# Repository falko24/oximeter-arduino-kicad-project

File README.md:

<div align="center">

# 🩺 Pulse Oximeter & OLED Interface
### Complete PCB Design for Arduino Nano & MAX30102

*Kompaktowy, dwuwarstwowy moduł PCB pulsooksymetru zintegrowany z wyświetlaczem OLED oraz przyciskami sterującymi.*

</div>

---

## 📸 Podgląd projektu

| Widok 3D (Front) | Widok 3D (Back) |
| :---: | :---: |
|  |  |

---

## 🛠️ Specyfikacja techniczna

* **Mikrokontroler:** Arduino Nano v3 (ATmega328P)
* **Czujnik tętna i SpO2:** MAX30102 (I2C)
* **Wyświetlacz:** OLED 0.96" SSD1306 / 128x64 px (I2C)
* **Interfejs użytkownika:** 3x przyciski Tact Switch ze sprzętową filtracją drgań styków (RC)
* **Wymiary PCB:** 2-warstwowa płyta FR4 (grubość $1.6\text{ mm}$)
* **Zasilanie:** 5V z portu USB Arduino Nano

---

## 🗂️ Struktura repozytorium

```text
.
├── docs/           # Wyrenderowane zdjęcia 3D projektu
├── gerber/         # Paczka produkcyjna (gerber.zip) gotowa do zamówienia
└── hardware/       # Pliki źródłowe KiCad (.kicad_pcb, .kicad_sch, .kicad_pro)

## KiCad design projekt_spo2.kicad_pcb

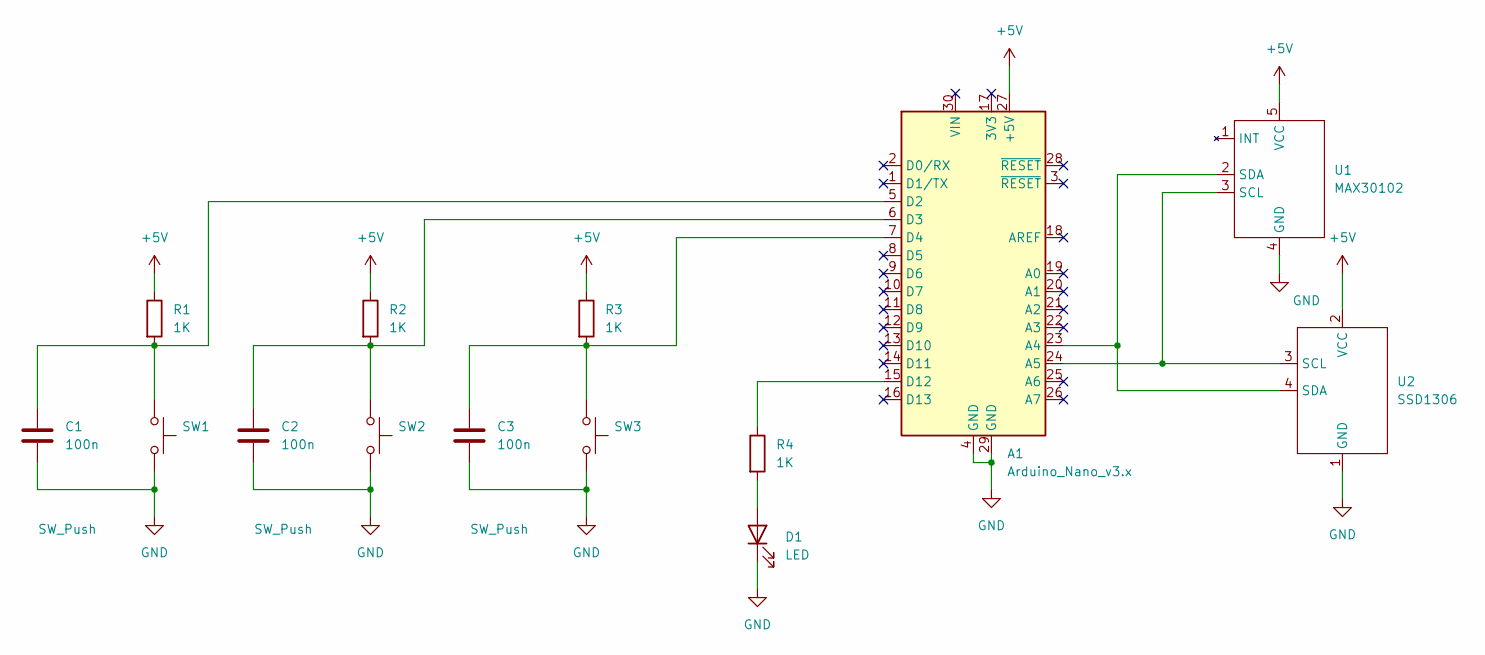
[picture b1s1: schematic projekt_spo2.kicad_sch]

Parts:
A1: Arduino_Nano_v3.x; Arduino_Nano
C1, C2, C3: 100n; C_1206_3216Metric
D1: LED; LED_1206_3216Metric
R1, R2, R3, R4: 1K; R_1206_3216Metric
SW1, SW2, SW3: SW_Push; SW_SPST_PTS645Sx43SMTR92
U1: MAX30102; MAX30102_MODULE
U2: SSD1306; SS1306

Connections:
+5V: A1.27 (+5V), R1.1, R2.1, R3.1, U1.5 (VCC), U2.2 (VCC)
GND: A1.4 (GND), A1.29 (GND), C1.2, C2.2, C3.2, D1.1 (K), SW1.2, SW2.2, SW3.2, U1.4 (GND), U2.1 (GND)
unnamed: A1.23 (A4), U1.2 (SDA), U2.4 (SDA)
unnamed: A1.24 (A5), U1.3 (SCL), U2.3 (SCL)
unnamed: A1.5 (D2), C1.1, R1.2, SW1.1
unnamed: A1.6 (D3), C2.1, R2.2, SW2.1
unnamed: A1.7 (D4), C3.1, R3.2, SW3.1
unnamed: A1.15 (D12), R4.1
unnamed: D1.2 (A), R4.2

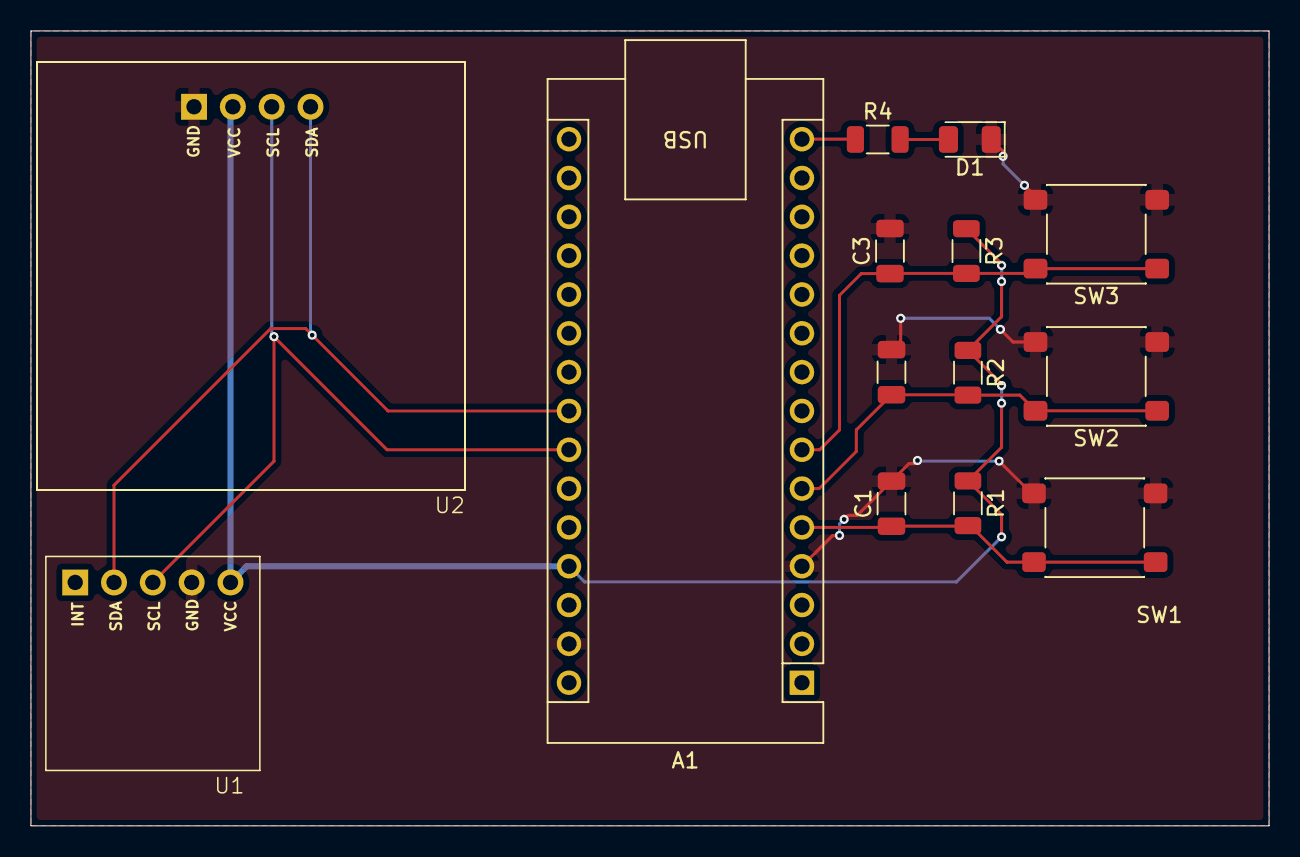
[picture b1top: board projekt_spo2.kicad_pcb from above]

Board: 4 copper layers, 81.0 x 52.0 mm, 14 parts (0 on the bottom side), 9 nets.

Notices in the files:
README.md:
License: MIT
